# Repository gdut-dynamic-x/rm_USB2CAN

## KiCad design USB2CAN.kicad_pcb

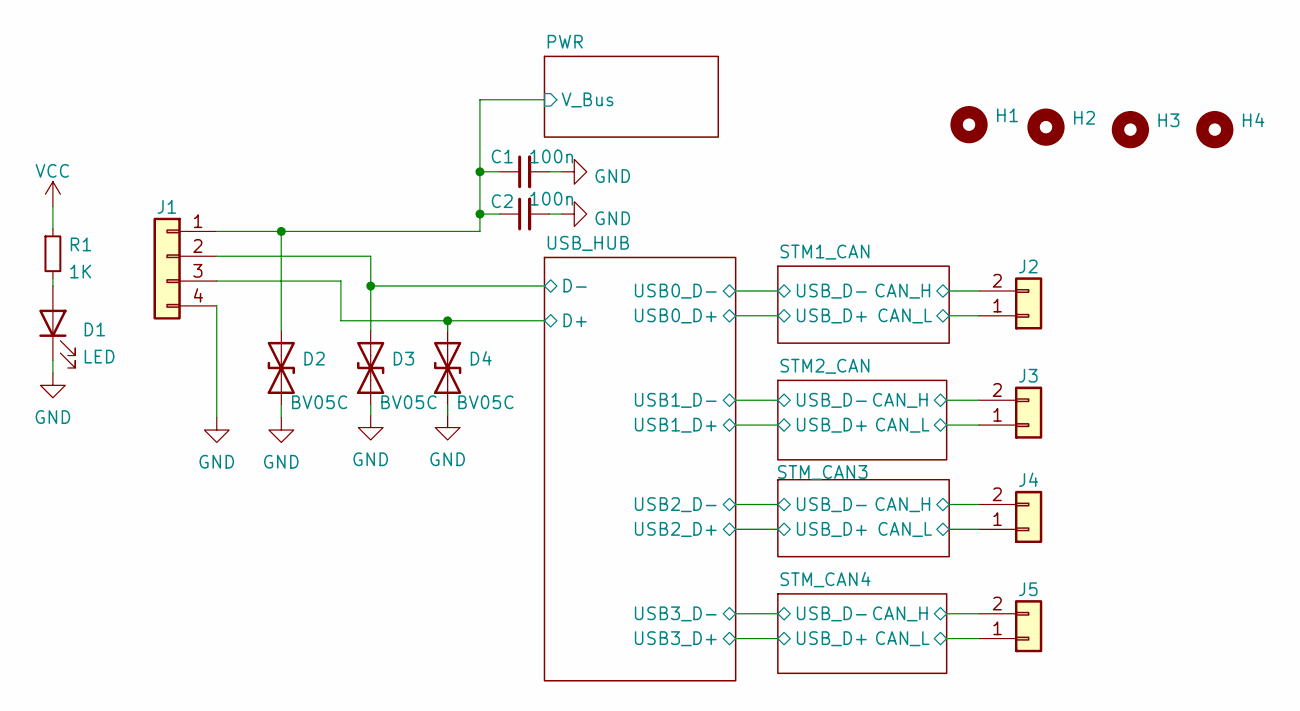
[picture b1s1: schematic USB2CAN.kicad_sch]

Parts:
C1, C2: 100n; C_0603_1608Metric
D1: LED; LED_0603_1608Metric
D2, D3, D4: BV05C; D_SOD-323
H1, H2, H3, H4: MountingHole; MountingHole_2.7mm_M2.5
J1: Conn_01x04; Molex_CLIK-Mate_502386-0470_1x04-1MP_P1.25mm_Horizontal
J2, J3, J4, J5: Conn_01x02; JST_GH_SM02B-GHS-TB_1x02-1MP_P1.25mm_Horizontal
R1: 1K; R_0603_1608Metric

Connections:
+5V: C1.1, C2.1, D2.2 (A2), J1.1; also elsewhere on the board
/STM1_CAN/CAN_H: J2.2; also elsewhere on the board
/STM1_CAN/CAN_L: J2.1; also elsewhere on the board
/STM2_CAN/CAN_H: J3.2; also elsewhere on the board
/STM2_CAN/CAN_L: J3.1; also elsewhere on the board
/STM_CAN3/CAN_H: J4.2; also elsewhere on the board
/STM_CAN3/CAN_L: J4.1; also elsewhere on the board
/STM_CAN4/CAN_H: J5.2; also elsewhere on the board
/STM_CAN4/CAN_L: J5.1; also elsewhere on the board
/USB_HUB/D+: D4.2 (A2), J1.3; also elsewhere on the board
/USB_HUB/D-: D3.2 (A2), J1.2; also elsewhere on the board
GND: C1.2, C2.2, D1.1 (K), D2.1 (A1), D3.1 (A1), D4.1 (A1), J1.4; also elsewhere on the board
unnamed: D1.2 (A), R1.2
VCC: R1.1; also elsewhere on the board

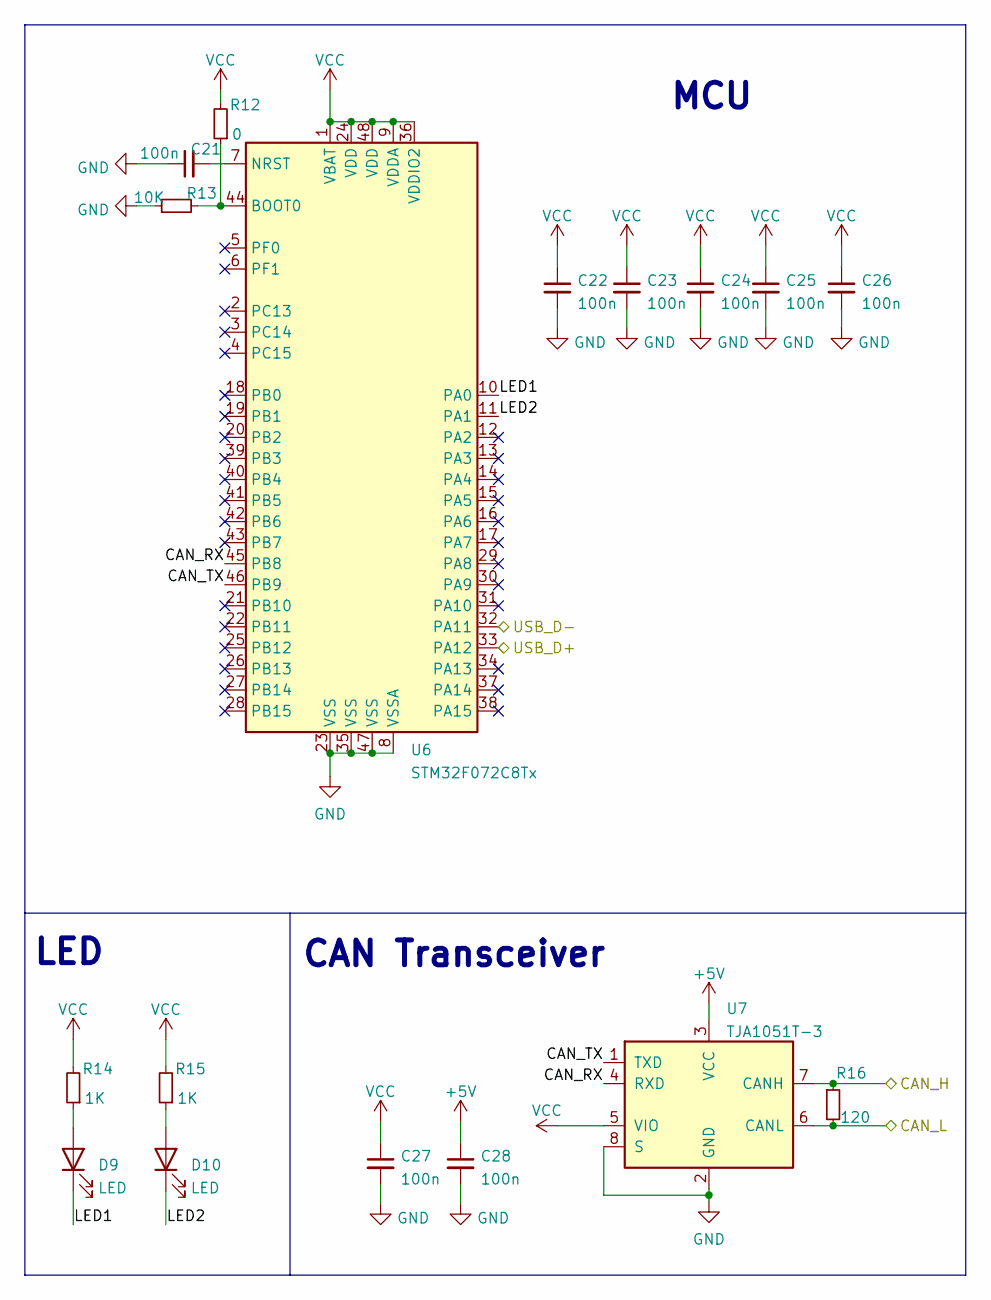
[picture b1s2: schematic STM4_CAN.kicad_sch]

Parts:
C21, C22, C23, C24, C25, C26, C27, C28: 100n; C_0603_1608Metric
D9, D10: LED; LED_0603_1608Metric
R12: 0; R_0603_1608Metric
R13: 10K; R_0603_1608Metric
R14, R15: 1K; R_0603_1608Metric
R16: 120; R_0603_1608Metric
U6: STM32F072C8Tx; LQFP-48_7x7mm_P0.5mm
U7: TJA1051T-3; SOIC-8_3.9x4.9mm_P1.27mm

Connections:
+5V: C28.1, U7.3 (VCC); also elsewhere on the board
/STM_CAN4/CAN_H: R16.1, U7.7 (CANH); also elsewhere on the board
/STM_CAN4/CAN_L: R16.2, U7.6 (CANL); also elsewhere on the board
/STM_CAN4/CAN_RX: U6.45 (PB8), U7.4 (RXD)
/STM_CAN4/CAN_TX: U6.46 (PB9), U7.1 (TXD)
/STM_CAN4/LED1: D9.1 (K), U6.10 (PA0)
/STM_CAN4/LED2: D10.1 (K), U6.11 (PA1)
/STM_CAN4/USB_D+: U6.33 (PA12); also elsewhere on the board
/STM_CAN4/USB_D-: U6.32 (PA11); also elsewhere on the board
GND: C21.1, C22.2, C23.2, C24.2, C25.2, C26.2, C27.2, C28.2, R13.1, U6.8 (VSSA), U6.23 (VSS), U6.35 (VSS), U6.47 (VSS), U7.2 (GND), U7.8 (S); also elsewhere on the board
unnamed: C21.2, U6.7 (NRST)
unnamed: D9.2 (A), R14.1
unnamed: D10.2 (A), R15.1
unnamed: R12.1, R13.2, U6.44 (BOOT0)
VCC: C22.1, C23.1, C24.1, C25.1, C26.1, C27.1, R12.2, R14.2, R15.2, U6.1 (VBAT), U6.9 (VDDA), U6.24 (VDD), U6.36 (VDDIO2), U6.48 (VDD), U7.5 (VIO); also elsewhere on the board

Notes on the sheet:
MCU
LED
CAN Transceiver

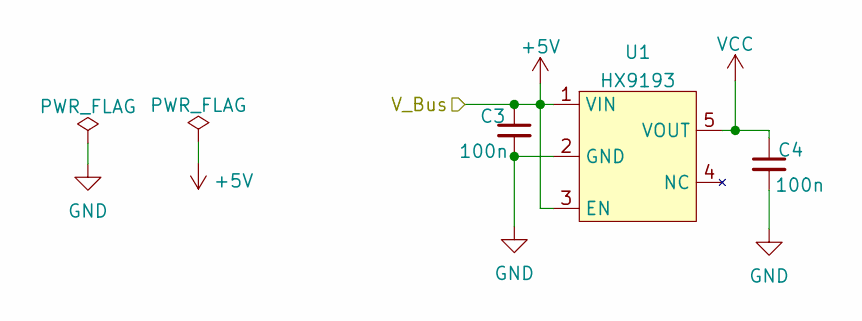
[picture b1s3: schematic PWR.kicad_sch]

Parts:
C3, C4: 100n; C_0603_1608Metric
U1: HX9193; SOT-23-5_HandSoldering

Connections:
+5V: C3.1, U1.1 (VIN), U1.3 (EN); also elsewhere on the board
GND: C3.2, C4.2, U1.2 (GND); also elsewhere on the board
VCC: C4.1, U1.5 (VOUT); also elsewhere on the board

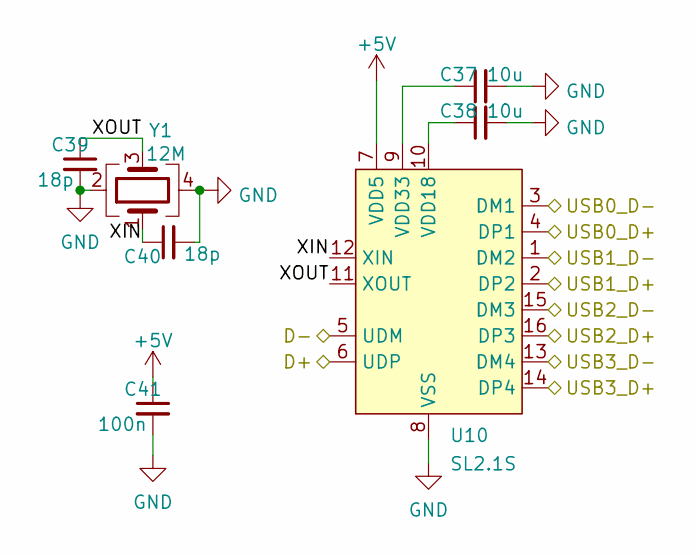
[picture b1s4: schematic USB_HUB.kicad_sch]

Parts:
C37, C38: 10u; C_0603_1608Metric
C39, C40: 18p; C_0603_1608Metric
C41: 100n; C_0603_1608Metric
U10: SL2.1S; SL2.1S-SSOP-16
Y1: 12M; Crystal_SMD_3225-4Pin_3.2x2.5mm

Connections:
+5V: C41.1, U10.7 (VDD5); also elsewhere on the board
/STM1_CAN/USB_D+: U10.4 (DP1); also elsewhere on the board
/STM1_CAN/USB_D-: U10.3 (DM1); also elsewhere on the board
/STM2_CAN/USB_D+: U10.2 (DP2); also elsewhere on the board
/STM2_CAN/USB_D-: U10.1 (DM2); also elsewhere on the board
/STM_CAN3/USB_D+: U10.16 (DP3); also elsewhere on the board
/STM_CAN3/USB_D-: U10.15 (DM3); also elsewhere on the board
/STM_CAN4/USB_D+: U10.14 (DP4); also elsewhere on the board
/STM_CAN4/USB_D-: U10.13 (DM4); also elsewhere on the board
/USB_HUB/D+: U10.6 (UDP); also elsewhere on the board
/USB_HUB/D-: U10.5 (UDM); also elsewhere on the board
/USB_HUB/XIN: C40.1, U10.12 (XIN), Y1.1
/USB_HUB/XOUT: C39.1, U10.11 (XOUT), Y1.3
GND: C37.2, C38.2, C39.2, C40.2, C41.2, U10.8 (VSS), Y1.2, Y1.4; also elsewhere on the board
unnamed: C37.1, U10.9 (VDD33)
unnamed: C38.1, U10.10 (VDD18)

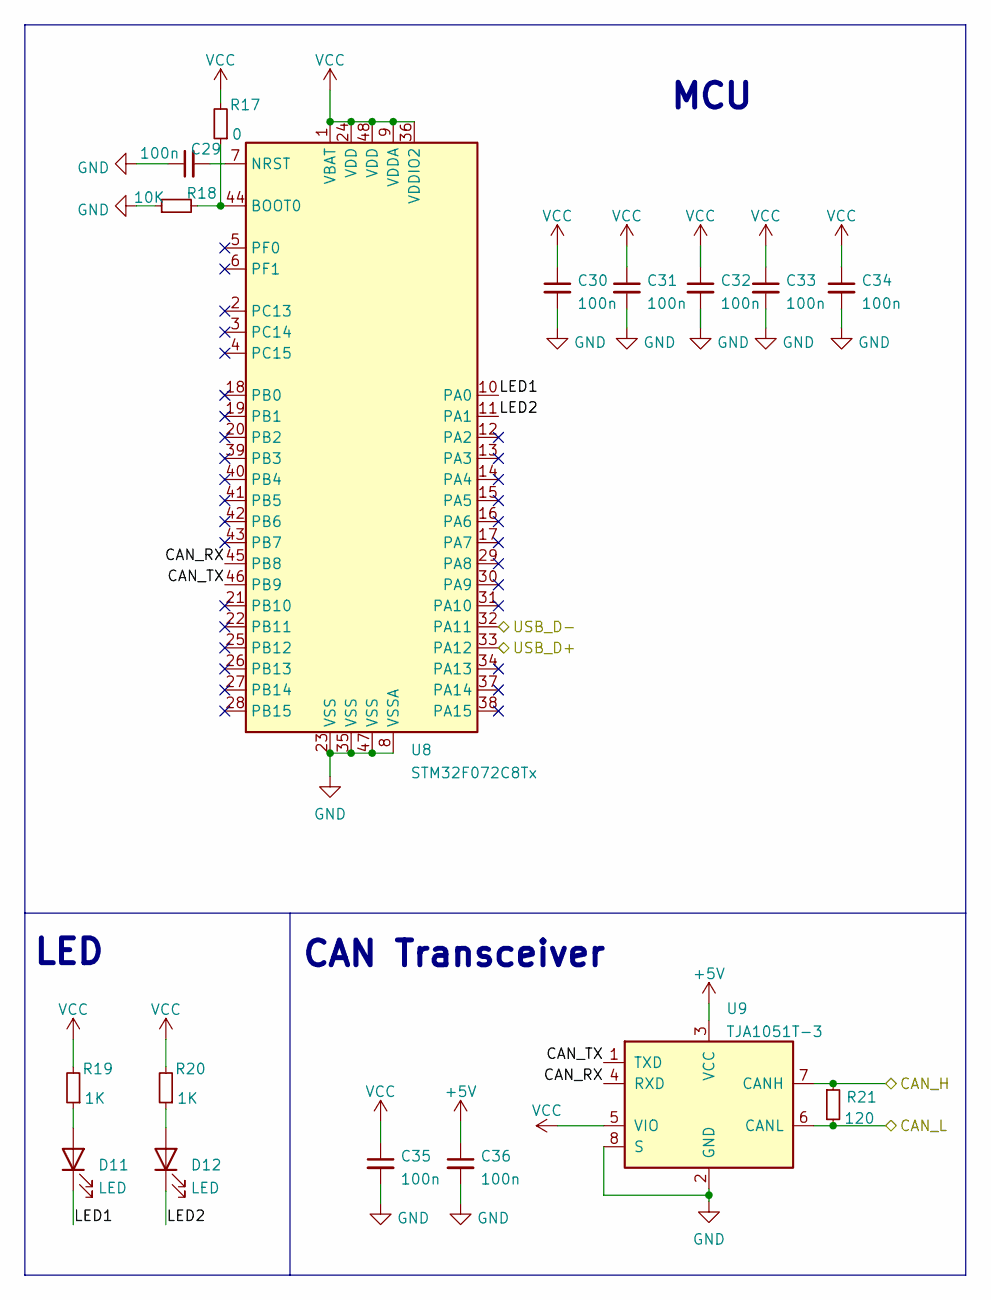
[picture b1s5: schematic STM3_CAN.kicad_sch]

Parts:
C29, C30, C31, C32, C33, C34, C35, C36: 100n; C_0603_1608Metric
D11, D12: LED; LED_0603_1608Metric
R17: 0; R_0603_1608Metric
R18: 10K; R_0603_1608Metric
R19, R20: 1K; R_0603_1608Metric
R21: 120; R_0603_1608Metric
U8: STM32F072C8Tx; LQFP-48_7x7mm_P0.5mm
U9: TJA1051T-3; SOIC-8_3.9x4.9mm_P1.27mm

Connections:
+5V: C36.1, U9.3 (VCC); also elsewhere on the board
/STM_CAN3/CAN_H: R21.1, U9.7 (CANH); also elsewhere on the board
/STM_CAN3/CAN_L: R21.2, U9.6 (CANL); also elsewhere on the board
/STM_CAN3/CAN_RX: U8.45 (PB8), U9.4 (RXD)
/STM_CAN3/CAN_TX: U8.46 (PB9), U9.1 (TXD)
/STM_CAN3/LED1: D11.1 (K), U8.10 (PA0)
/STM_CAN3/LED2: D12.1 (K), U8.11 (PA1)
/STM_CAN3/USB_D+: U8.33 (PA12); also elsewhere on the board
/STM_CAN3/USB_D-: U8.32 (PA11); also elsewhere on the board
GND: C29.1, C30.2, C31.2, C32.2, C33.2, C34.2, C35.2, C36.2, R18.1, U8.8 (VSSA), U8.23 (VSS), U8.35 (VSS), U8.47 (VSS), U9.2 (GND), U9.8 (S); also elsewhere on the board
unnamed: C29.2, U8.7 (NRST)
unnamed: D11.2 (A), R19.1
unnamed: D12.2 (A), R20.1
unnamed: R17.1, R18.2, U8.44 (BOOT0)
VCC: C30.1, C31.1, C32.1, C33.1, C34.1, C35.1, R17.2, R19.2, R20.2, U8.1 (VBAT), U8.9 (VDDA), U8.24 (VDD), U8.36 (VDDIO2), U8.48 (VDD), U9.5 (VIO); also elsewhere on the board

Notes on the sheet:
CAN Transceiver
LED
MCU

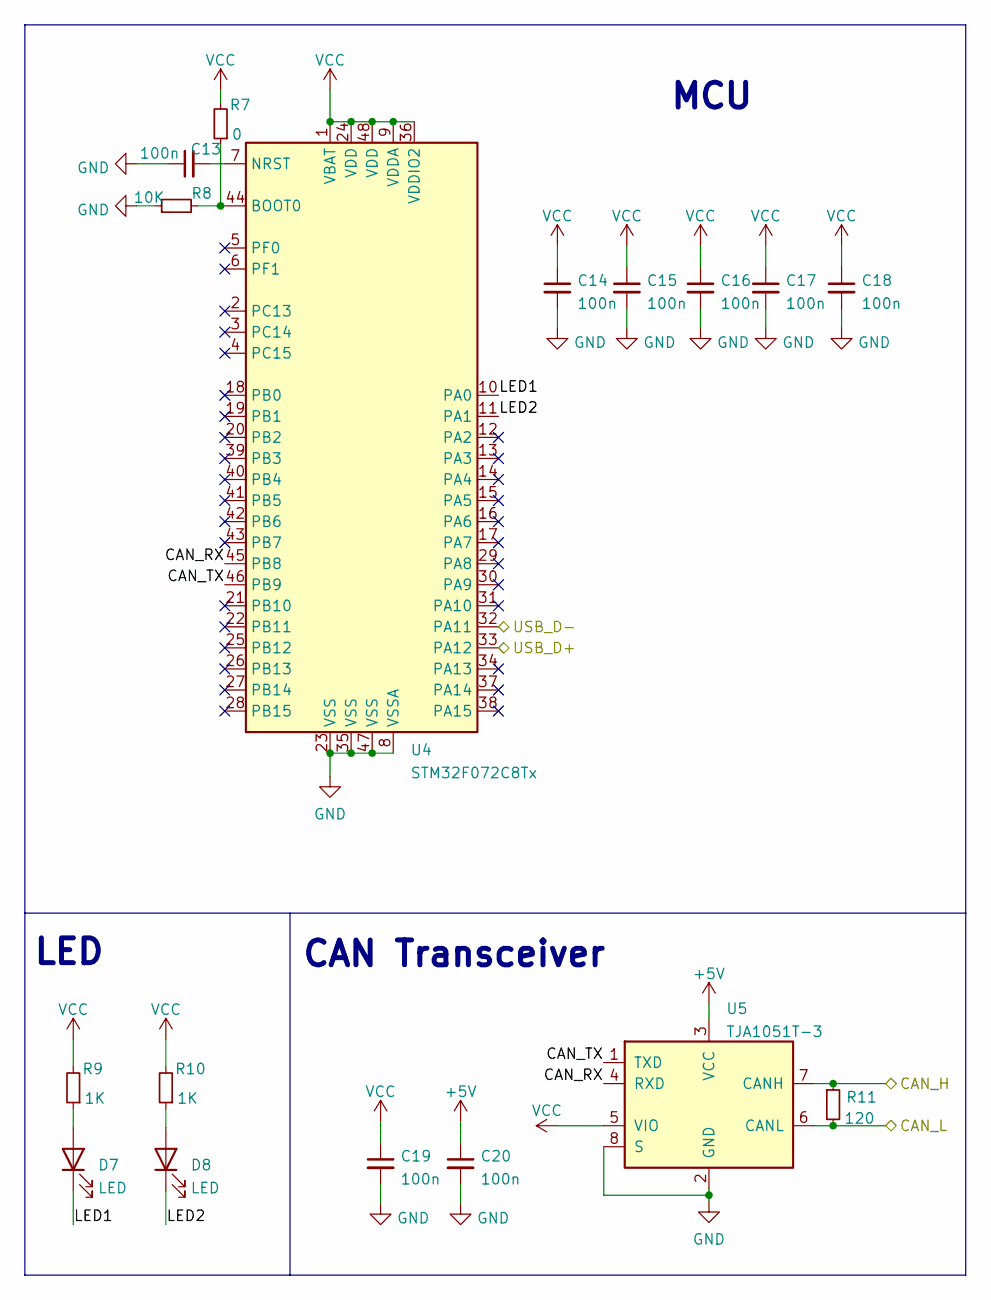
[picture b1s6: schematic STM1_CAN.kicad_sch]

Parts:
C13, C14, C15, C16, C17, C18, C19, C20: 100n; C_0603_1608Metric
D7, D8: LED; LED_0603_1608Metric
R7: 0; R_0603_1608Metric
R8: 10K; R_0603_1608Metric
R9, R10: 1K; R_0603_1608Metric
R11: 120; R_0603_1608Metric
U4: STM32F072C8Tx; LQFP-48_7x7mm_P0.5mm
U5: TJA1051T-3; SOIC-8_3.9x4.9mm_P1.27mm

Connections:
+5V: C20.1, U5.3 (VCC); also elsewhere on the board
/STM1_CAN/CAN_H: R11.1, U5.7 (CANH); also elsewhere on the board
/STM1_CAN/CAN_L: R11.2, U5.6 (CANL); also elsewhere on the board
/STM1_CAN/CAN_RX: U4.45 (PB8), U5.4 (RXD)
/STM1_CAN/CAN_TX: U4.46 (PB9), U5.1 (TXD)
/STM1_CAN/LED1: D7.1 (K), U4.10 (PA0)
/STM1_CAN/LED2: D8.1 (K), U4.11 (PA1)
/STM1_CAN/USB_D+: U4.33 (PA12); also elsewhere on the board
/STM1_CAN/USB_D-: U4.32 (PA11); also elsewhere on the board
GND: C13.1, C14.2, C15.2, C16.2, C17.2, C18.2, C19.2, C20.2, R8.1, U4.8 (VSSA), U4.23 (VSS), U4.35 (VSS), U4.47 (VSS), U5.2 (GND), U5.8 (S); also elsewhere on the board
unnamed: C13.2, U4.7 (NRST)
unnamed: D7.2 (A), R9.1
unnamed: D8.2 (A), R10.1
unnamed: R7.1, R8.2, U4.44 (BOOT0)
VCC: C14.1, C15.1, C16.1, C17.1, C18.1, C19.1, R7.2, R9.2, R10.2, U4.1 (VBAT), U4.9 (VDDA), U4.24 (VDD), U4.36 (VDDIO2), U4.48 (VDD), U5.5 (VIO); also elsewhere on the board

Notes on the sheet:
CAN Transceiver
LED
MCU

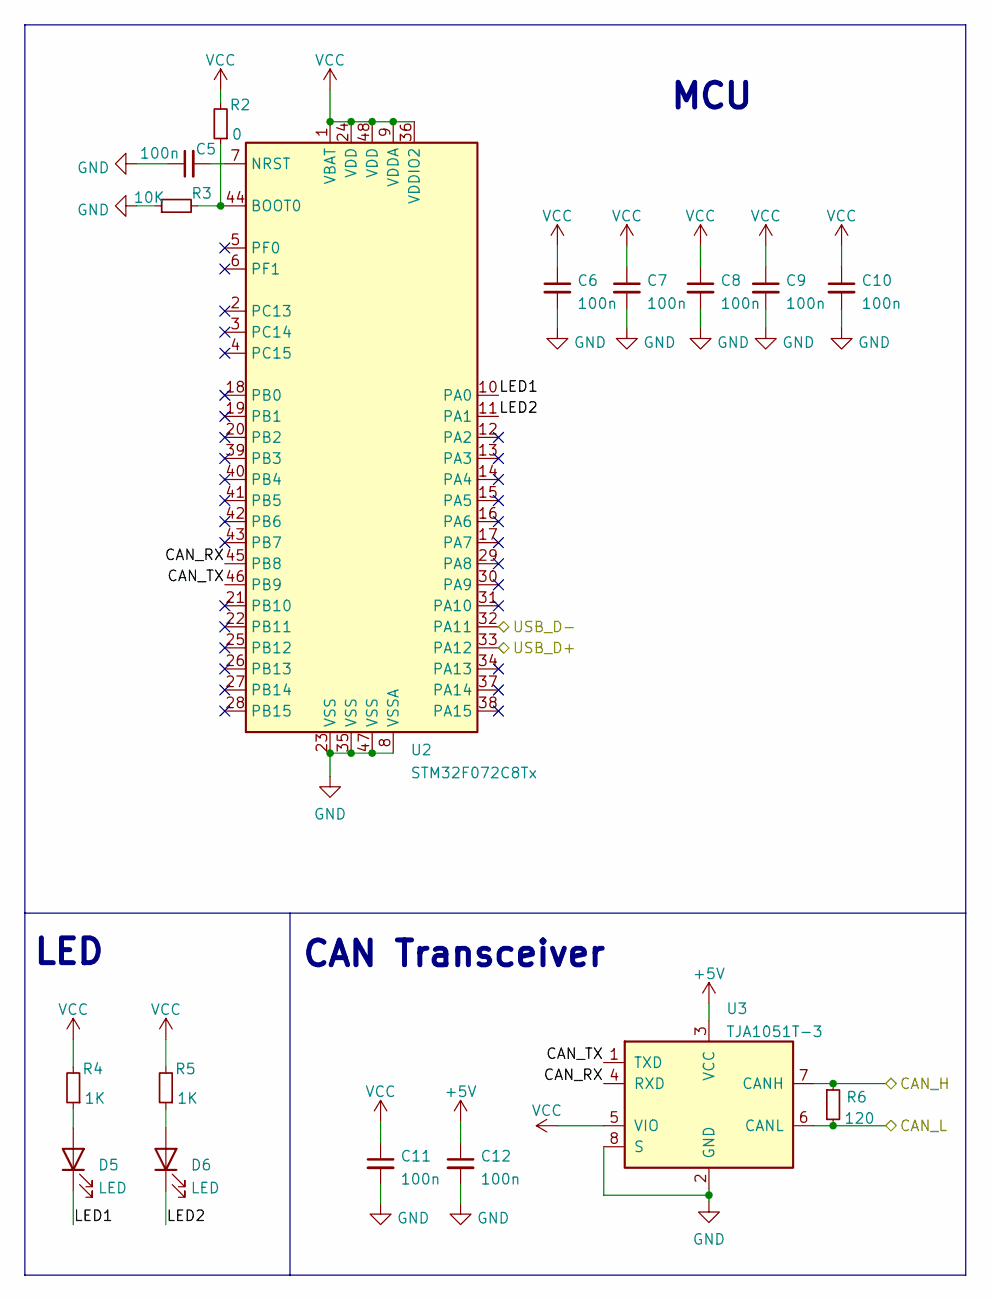
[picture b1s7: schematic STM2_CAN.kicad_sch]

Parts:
C5, C6, C7, C8, C9, C10, C11, C12: 100n; C_0603_1608Metric
D5, D6: LED; LED_0603_1608Metric
R2: 0; R_0603_1608Metric
R3: 10K; R_0603_1608Metric
R4, R5: 1K; R_0603_1608Metric
R6: 120; R_0603_1608Metric
U2: STM32F072C8Tx; LQFP-48_7x7mm_P0.5mm
U3: TJA1051T-3; SOIC-8_3.9x4.9mm_P1.27mm

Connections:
+5V: C12.1, U3.3 (VCC); also elsewhere on the board
/STM2_CAN/CAN_H: R6.1, U3.7 (CANH); also elsewhere on the board
/STM2_CAN/CAN_L: R6.2, U3.6 (CANL); also elsewhere on the board
/STM2_CAN/CAN_RX: U2.45 (PB8), U3.4 (RXD)
/STM2_CAN/CAN_TX: U2.46 (PB9), U3.1 (TXD)
/STM2_CAN/LED1: D5.1 (K), U2.10 (PA0)
/STM2_CAN/LED2: D6.1 (K), U2.11 (PA1)
/STM2_CAN/USB_D+: U2.33 (PA12); also elsewhere on the board
/STM2_CAN/USB_D-: U2.32 (PA11); also elsewhere on the board
GND: C5.1, C6.2, C7.2, C8.2, C9.2, C10.2, C11.2, C12.2, R3.1, U2.8 (VSSA), U2.23 (VSS), U2.35 (VSS), U2.47 (VSS), U3.2 (GND), U3.8 (S); also elsewhere on the board
unnamed: C5.2, U2.7 (NRST)
unnamed: D5.2 (A), R4.1
unnamed: D6.2 (A), R5.1
unnamed: R2.1, R3.2, U2.44 (BOOT0)
VCC: C6.1, C7.1, C8.1, C9.1, C10.1, C11.1, R2.2, R4.2, R5.2, U2.1 (VBAT), U2.9 (VDDA), U2.24 (VDD), U2.36 (VDDIO2), U2.48 (VDD), U3.5 (VIO); also elsewhere on the board

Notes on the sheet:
MCU
LED
CAN Transceiver

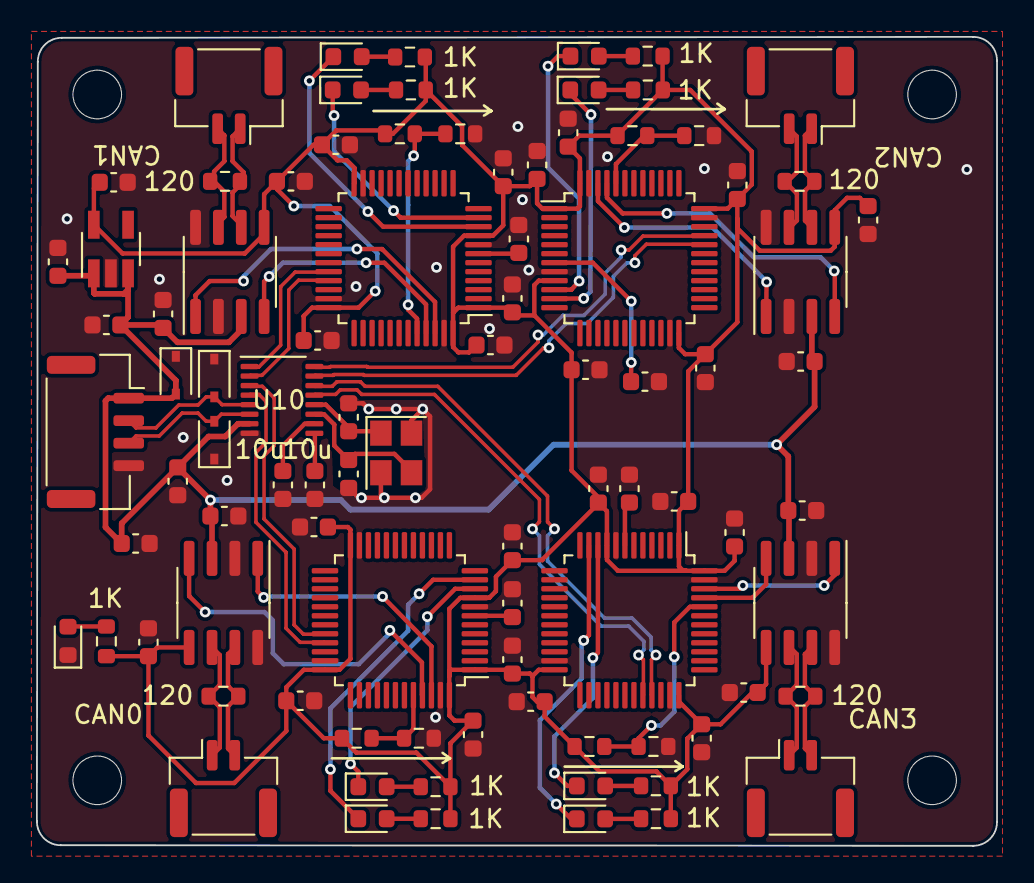
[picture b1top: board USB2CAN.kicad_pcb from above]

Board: 2 copper layers, 53.3 x 44.9 mm, 94 parts (0 on the bottom side), 58 nets.

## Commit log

2022-05-20 Add USB2CAN
2022-05-20 Turn overall Lib to local Lib to avoid incorrect display of schematics
